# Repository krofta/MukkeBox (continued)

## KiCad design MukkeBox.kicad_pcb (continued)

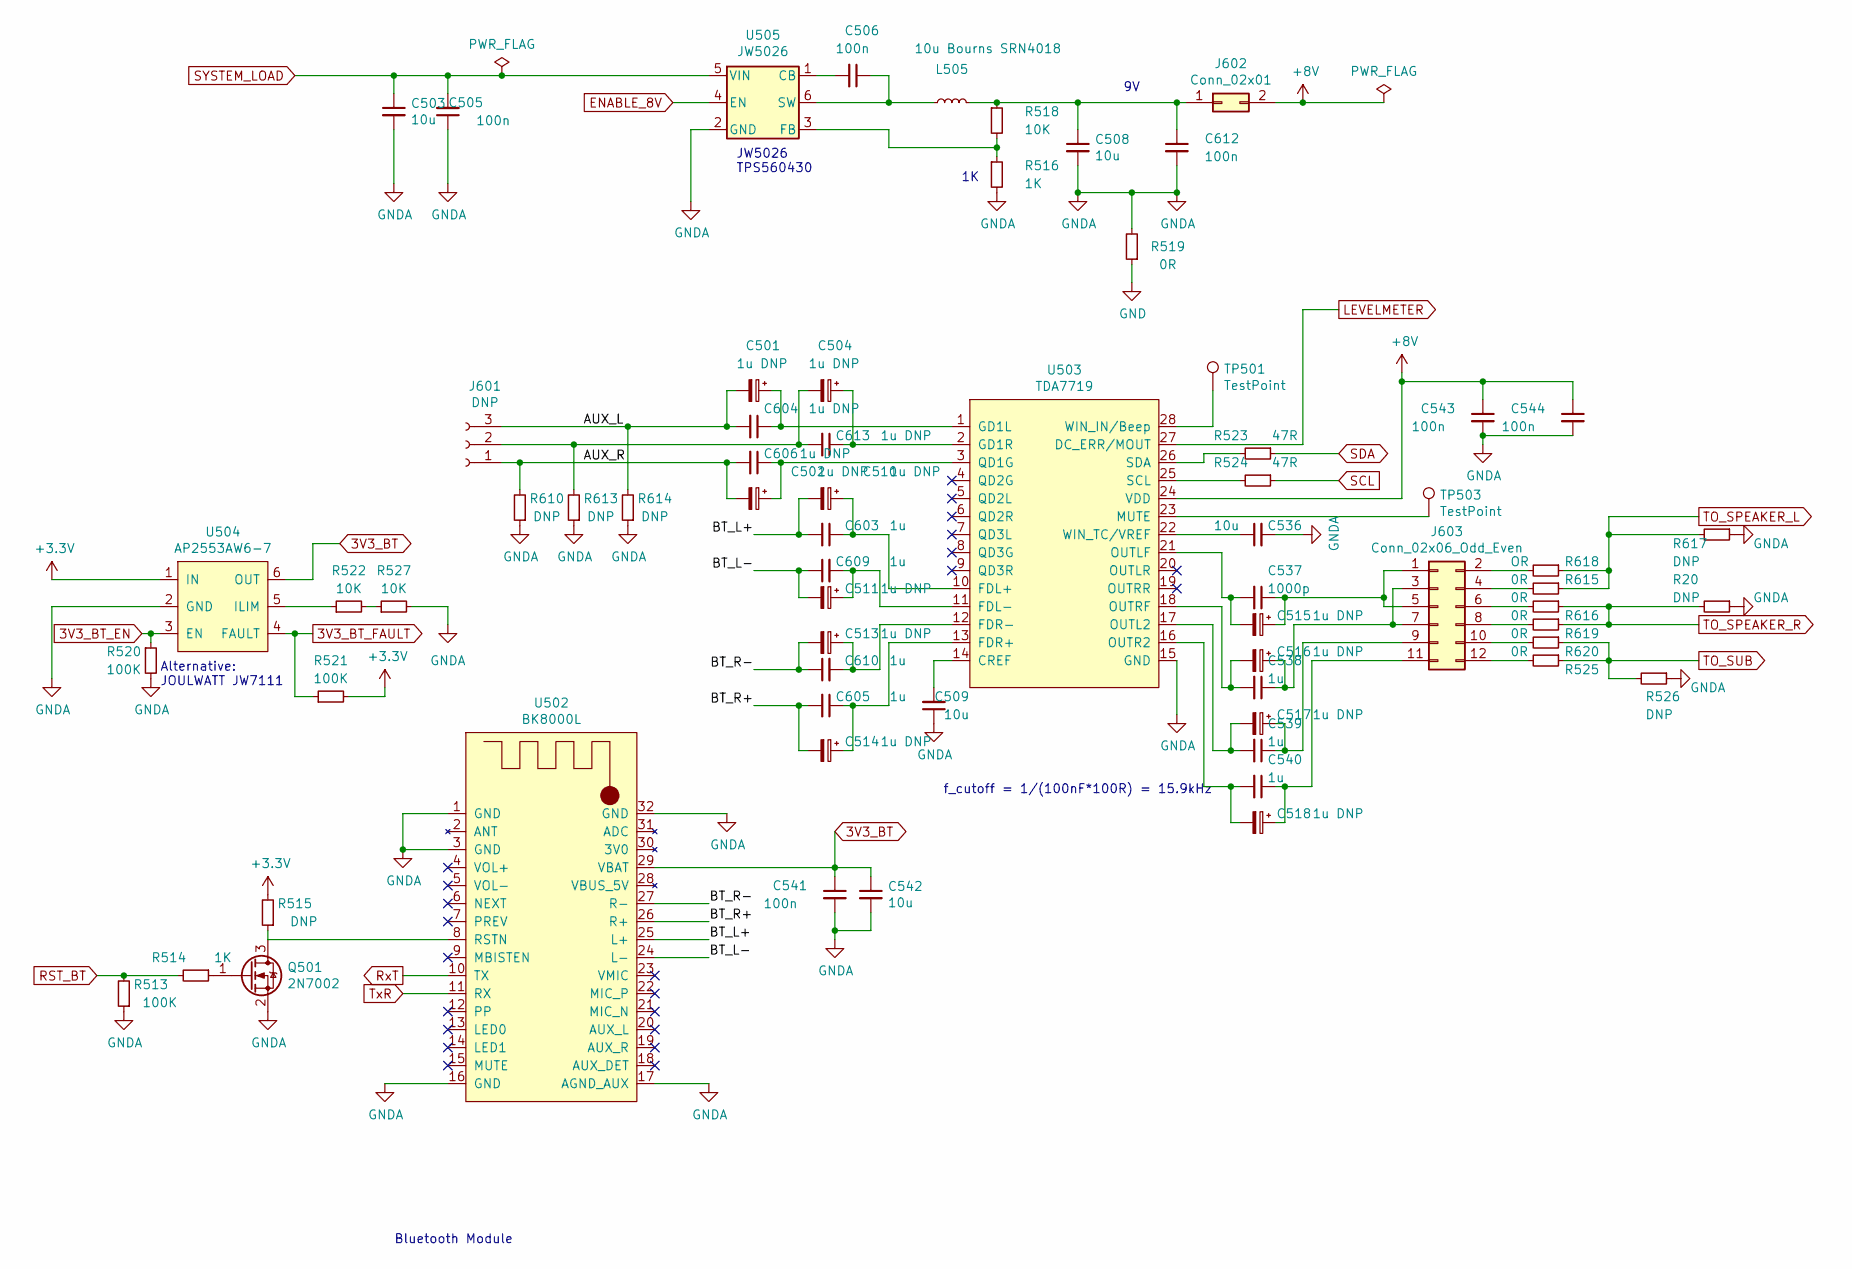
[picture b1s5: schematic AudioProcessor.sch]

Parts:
C501, C502, C504, C510, C511, C513, C514, C515, C516, C517, C518: 1u DNP; CP_EIA-3216-18_Kemet-A
C503, C508, C509, C536, C542: 10u; C_1206_3216Metric_Pad1.42x1.75mm_HandSolder
C505, C506, C541, C543, C544, C612: 100n; C_0603_1608Metric_Pad1.05x0.95mm_HandSolder
C537: 1000p; C_Rect_L7.2mm_W3.5mm_P5.00mm_FKS2_FKP2_MKS2_MKP2
C538, C539, C540, C603, C605, C609, C610: 1u; C_Rect_L7.2mm_W3.5mm_P5.00mm_FKS2_FKP2_MKS2_MKP2
C604, C606, C613: 1u DNP; C_Rect_L7.2mm_W3.5mm_P5.00mm_FKS2_FKP2_MKS2_MKP2
J601: DNP; PinHeader_1x03_P2.54mm_Vertical
J602: Conn_02x01; PinHeader_1x02_P2.54mm_Vertical
J603: Conn_02x06_Odd_Even; PinHeader_2x06_P2.54mm_Vertical
L505: 10u Bourns SRN4018; L_Bourns-SRN4018
Q501: 2N7002; SOT-23
R20, R515, R526, R610, R613, R614, R617: DNP; R_0603_1608Metric_Pad1.05x0.95mm_HandSolder
R513, R520, R521: 100K; R_0603_1608Metric_Pad1.05x0.95mm_HandSolder
R514, R516: 1K; R_0603_1608Metric_Pad1.05x0.95mm_HandSolder
R518, R522, R527: 10K; R_0603_1608Metric_Pad1.05x0.95mm_HandSolder
R519: 0R; R_1206_3216Metric_Pad1.42x1.75mm_HandSolder
R523, R524: 47R; R_0603_1608Metric_Pad1.05x0.95mm_HandSolder
R525, R615, R616, R619, R620: 0R; R_0603_1608Metric_Pad1.05x0.95mm_HandSolder
R618: OR; R_0603_1608Metric_Pad1.05x0.95mm_HandSolder
TP501, TP503: TestPoint; TestPoint_Pad_1.0x1.0mm
U502: BK8000L
U503: TDA7719; TSSOP-28_4.4x9.7mm_P0.65mm
U504: AP2553AW6-7; TSOT-23-6
U505: JW5026; SOT-23-6_Handsoldering

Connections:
3V3_BT: C541.1, C542.1, U502.29 (VBAT), U504.6 (OUT)
3V3_BT_EN: R520.1, U504.3 (EN); also elsewhere on the board
3V3_BT_FAULT: R521.1, U504.4 (FAULT); also elsewhere on the board
+8V: C543.1, C544.1, J602.2, U503.24 (VDD)
/AudioProcessor/AUX_L: C501.2, C604.2, J601.3, R614.2
/AudioProcessor/AUX_R: C502.2, C606.2, J601.1, R610.2
/AudioProcessor/BT_L+: C510.2, C603.2, U502.25 (L+)
/AudioProcessor/BT_L-: C511.2, C609.1, U502.24 (L-)
/AudioProcessor/BT_R+: C514.2, C605.2, U502.26 (R+)
/AudioProcessor/BT_R-: C513.2, C610.1, U502.27 (R-)
ENABLE_8V: U505.4 (EN); also elsewhere on the board
GND: R519.1; also elsewhere on the board
GNDA: C503.2, C505.1, C508.2, C509.1, C536.2, C541.2, C542.2, C543.2, C544.2, C612.2, Q501.2 (S), R20.1, R513.1, R516.2, R519.2, R520.2, R526.1, R527.2, R610.1, R613.1, R614.1, R617.1, U502.1 (GND), U502.3 (GND), U502.16 (GND), U502.17 (AGND_AUX), U502.32 (GND), U503.15 (GND), U504.2 (GND), U505.2 (GND); also elsewhere on the board
LEVELMETER: U503.27 (DC_ERR/MOUT); also elsewhere on the board
unnamed: C501.1, C604.1, U503.1 (GD1L)
unnamed: C502.1, C606.1, U503.3 (QD1G)
unnamed: C504.1, C613.1, U503.2 (GD1R)
unnamed: C504.2, C613.2, J601.2, R613.2
unnamed: C506.1, L505.1, U505.6 (SW)
unnamed: C506.2, U505.1 (CB)
unnamed: C508.1, C612.1, J602.1, L505.2, R518.1
unnamed: C509.2, U503.14 (CREF)
unnamed: C510.1, C603.1, U503.10 (FDL+)
unnamed: C511.1, C609.2, U503.11 (FDL-)
unnamed: C513.1, C610.2, U503.12 (FDR-)
unnamed: C514.1, C605.1, U503.13 (FDR+)
unnamed: C515.1, C537.1, J603.1, J603.5
unnamed: C515.2, C537.2, U503.21 (OUTLF)
unnamed: C516.1, C538.1, J603.3, J603.7
unnamed: C516.2, C538.2, U503.18 (OUTRF)
unnamed: C517.1, C539.1, J603.9
unnamed: C517.2, C539.2, U503.17 (OUTL2)
unnamed: C518.1, C540.1, J603.11
unnamed: C518.2, C540.2, U503.16 (OUTR2)
unnamed: C536.1, U503.22 (WIN_TC/VREF)
unnamed: J603.2, R618.2
unnamed: J603.4, R615.2
unnamed: J603.6, R616.2
unnamed: J603.8, R619.2
unnamed: J603.10, R620.2
unnamed: J603.12, R525.2
unnamed: Q501.1 (G), R514.1
unnamed: Q501.3 (D), R515.1, U502.8 (RSTN)
unnamed: R516.1, R518.2, U505.3 (FB)
unnamed: R522.1, U504.5 (ILIM)
unnamed: R522.2, R527.1
unnamed: R523.2, U503.26 (SDA)
unnamed: R524.2, U503.25 (SCL)
unnamed: TP501.1, U503.28 (WIN_IN/Beep)
unnamed: TP503.1, U503.23 (MUTE)
RST_BT: R513.2, R514.2; also elsewhere on the board
RxT: U502.10 (TX); also elsewhere on the board
SCL: R524.1; also elsewhere on the board
SDA: R523.1; also elsewhere on the board
SYSTEM_LOAD: C503.1, C505.2, U505.5 (VIN); also elsewhere on the board
TO_SPEAKER_L: R615.1, R617.2, R618.1; also elsewhere on the board
TO_SPEAKER_R: R20.2, R616.1, R619.1; also elsewhere on the board
TO_SUB: R525.1, R526.2, R620.1; also elsewhere on the board
TxR: U502.11 (RX); also elsewhere on the board

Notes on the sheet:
f_cutoff = 1/(100nF*100R) = 15.9kHz
Bluetooth Module
JW5026 TPS560430
Alternative: JOULWATT JW7111

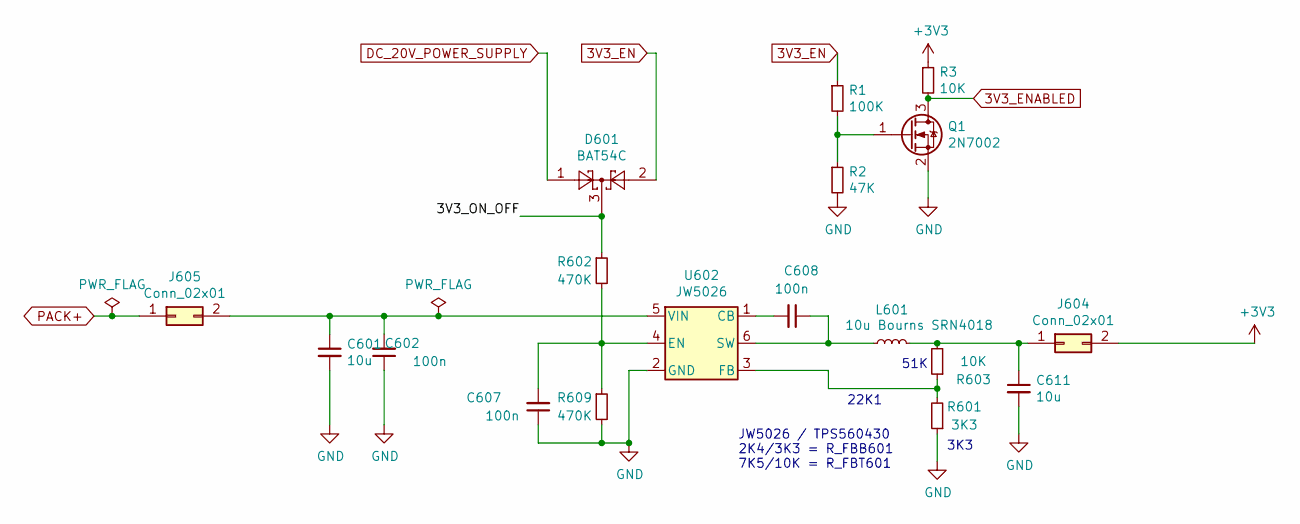
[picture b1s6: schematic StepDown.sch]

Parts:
C601, C611: 10u; C_1206_3216Metric_Pad1.42x1.75mm_HandSolder
C602, C607, C608: 100n; C_0603_1608Metric_Pad1.05x0.95mm_HandSolder
D601: BAT54C; SOT-23
J604, J605: Conn_02x01; PinHeader_1x02_P2.54mm_Vertical
L601: 10u Bourns SRN4018; L_Bourns-SRN4018
Q1: 2N7002; SOT-23
R1: 100K; R_0603_1608Metric_Pad1.05x0.95mm_HandSolder
R2: 47K; R_0603_1608Metric_Pad1.05x0.95mm_HandSolder
R3, R603: 10K; R_0603_1608Metric_Pad1.05x0.95mm_HandSolder
R601: 3K3; R_0603_1608Metric_Pad1.05x0.95mm_HandSolder
R602, R609: 470K; R_0603_1608Metric_Pad1.05x0.95mm_HandSolder
U602: JW5026; SOT-23-6_Handsoldering

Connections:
3V3_EN: D601.2, R1.1; also elsewhere on the board
3V3_ENABLED: Q1.3 (D), R3.2; also elsewhere on the board
/StepDown/3V3_ON_OFF: D601.3, R602.1
DC_20V_POWER_SUPPLY: D601.1; also elsewhere on the board
GND: C601.2, C602.1, C607.1, C611.2, Q1.2 (S), R2.2, R601.1, R609.2, U602.2 (GND); also elsewhere on the board
unnamed: C601.1, C602.2, J605.2, U602.5 (VIN)
unnamed: C607.2, R602.2, R609.1, U602.4 (EN)
unnamed: C608.1, L601.1, U602.6 (SW)
unnamed: C608.2, U602.1 (CB)
unnamed: C611.1, J604.1, L601.2, R603.2
unnamed: Q1.1 (G), R1.2, R2.1
unnamed: R601.2, R603.1, U602.3 (FB)
PACK+: J605.1; also elsewhere on the board

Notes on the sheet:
51K
22K1
JW5026 / TPS560430 2K4/3K3 = R_FBB601 7K5/10K = R_FBT601
3K3

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
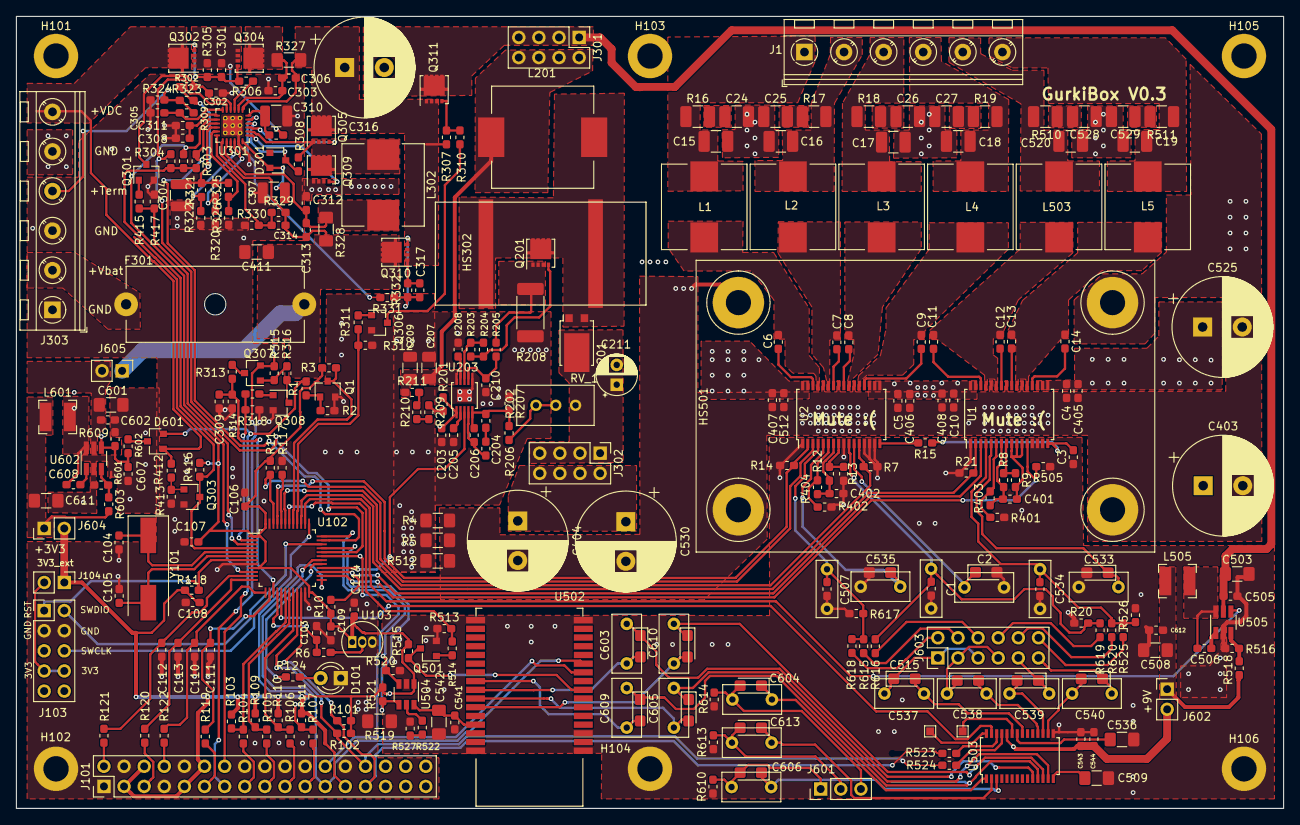
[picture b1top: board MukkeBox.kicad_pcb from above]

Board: 2 copper layers, 160.0 x 100.0 mm, 309 parts (0 on the bottom side), 204 nets.

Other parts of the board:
C317: 100n; C_0603_1608Metric_Pad1.05x0.95mm_HandSolder
R206: 47K; R_0603_1608Metric_Pad1.05x0.95mm_HandSolder
R207: 1K5; R_0603_1608Metric_Pad1.05x0.95mm_HandSolder
R208: R012; R_2512_6332Metric_Pad1.52x3.35mm_HandSolder
R209, R210, R211, R319, R321, R325, R330, R332: 100K; R_0603_1608Metric_Pad1.05x0.95mm_HandSolder
R320: 22K; R_0603_1608Metric_Pad1.05x0.95mm_HandSolder
R322, R323, R326: 10K; R_0603_1608Metric_Pad1.05x0.95mm_HandSolder
R324: 470K; R_0603_1608Metric_Pad1.05x0.95mm_HandSolder
R327, R328: 10m; R_1206_3216Metric_Pad1.42x1.75mm_HandSolder
R329: 700K; R_0603_1608Metric_Pad1.05x0.95mm_HandSolder
R331: 1K; R_0603_1608Metric_Pad1.05x0.95mm_HandSolder

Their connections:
/00_Charger/SRP: R328.1; also elsewhere on the board
/00_Charger/TS: R323.1, R324.2; also elsewhere on the board
/00_Charger/VREF: R319.2, R321.2, R323.2, R325.2; also elsewhere on the board
/02_StepUp/FB_BOOST: R206.1, R207.2; also elsewhere on the board
/02_StepUp/IN_STEPUP: R211.1; also elsewhere on the board
GND: R207.1, R208.1, R320.1, R322.1, R324.1, R326.1, R330.1; also elsewhere on the board
unnamed 86: R327.2; also elsewhere on the board
unnamed 88: C317.2, R327.1, R332.2; also elsewhere on the board
unnamed 92: R329.1, R330.2; also elsewhere on the board
unnamed 95: C317.1, R331.1, R332.1; also elsewhere on the board
unnamed 147: R208.2; also elsewhere on the board
unnamed 167: R209.2; also elsewhere on the board
unnamed 169: R206.2; also elsewhere on the board
unnamed: R209.1, R210.1
unnamed: R210.2, R211.2
unnamed 173: R319.1, R320.2; also elsewhere on the board
unnamed 174: R321.1, R322.2; also elsewhere on the board
unnamed 175: R325.1, R326.2; also elsewhere on the board
unnamed 176: R331.2; also elsewhere on the board
PACK+: R328.2, R329.2; also elsewhere on the board

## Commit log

2020-03-19 Charger Fertig
2020-03-22 BMS fertig, Charger fertig, Amplifier fertig. TODO: Charge vs Discharge LiPo wie machen sachen
2020-03-22 LDO für Audio DSP hinzugefügt
2020-04-01 3v3 über LDO von BMS enablen. Bluetooth hinzugefügt
2020-04-06 power schalter und taser hinzugefügt. Selbsthaltung LDO hinzugefügt. Gain Potis hinzugefügt, Separater Ground für Audio Lines
2020-04-10 Schaltplan fertig. Fertig für review
2020-04-10 Footprintzuordnung angefangen
2020-04-11 fast alle footprints herausgesucht. Spulen typen rausgesucht: Bourns spulen
2020-04-11 Port Expander und Rotary Encoder hinzugefügt. TODO: Footprint Heatsink Amp
2020-04-12 PCB angefangen: Charger geplaced
2020-04-12 Balancer geplaced
2020-04-12 Step Up geplaced
2020-04-12 Alle Parts geplaced: Dimension der Platine 200x105qmm. TODO Anzeige überarbeiten
2020-04-13 Mountingholes und Heatsinks hinzugefügt
2020-04-13 fertig zum routen
2020-04-13 Amp verdrahtet, Einige Layers verlegt
2020-04-14 Folienkondensatoren SMD gegen THT ausgetauscht. Kleine Fehler korrigiert
2020-04-16 layout fast fertig
2020-04-17 PCB fertig verdrahtet
2020-04-17 Fertig zum letzten Check vor Bestellung
2020-04-18 Board abgeschickt
2020-04-30 PartPlaceHelper hinzugefügt
2020-05-23 Letzter Kommit Version 0.1, Branch für neues Layout 0.2
2020-05-24 mute and stdby tda7498 geändert, tda7418 durch tda7719 ersetzt, xs3868 durch bk8000l ersetzt, 3v3 stepdown statt LDO. BMS gelöscht. TODO: Möglichkeit stepup und stepdown als modul aufzusetzen
2020-05-24 neue schematic fertig zum rewiew. DRC clean
2020-05-24 module, falls schaltung nicht funktioniert hinzugefügt
2020-05-25 3v3 regler ändern
2020-05-25 TODO: power on detect einfügen
2020-05-25 3v3 regler layout fertig
2020-05-28 vor änderungen von der Arbeit
2020-05-28 Nach Änderungen auf der Arbeit + anderes
2020-05-28 fertig
2020-06-02 Charger austauschen gegen bq24610
2020-06-02 Charger ausgetauscht, Mosfet und Dioden durch billigere ersetzt
2020-06-03 Änderungen Arbeit hinzugefügt: Layout neuer Charger
2020-06-03 Layout fertig, Schaltplan erneut checken
2020-06-04 Änderungen von der Arbeit, Viele LCSC Teile für teurere ausgetauscht
2020-06-06 Fast fertig TODO: Connector umverdrahten mit beschriftung
2020-06-06 Bestellung abgeschickt
2020-06-07 Bauteilwerte verändert
2020-06-29 Fehler bei Bestellung behoben: größere Vias. Platinen erfolgreich erhalten
2020-07-10 Bereit zur Bestellung
2020-07-10 Platine in X um 25mm verkürzt
2020-07-12 MukkePlatine auf EuroPlatinen groesse geändert
2020-07-12 fertig zum bestellen
2020-07-13 Footprints parallel zu Folienkondensatoren hinzugefügt; Bestellung ist abgeschickt!
2020-10-24 I2C Dreher behoben, BOM vereinfacht, 20dB Gain an ClassD Amps
